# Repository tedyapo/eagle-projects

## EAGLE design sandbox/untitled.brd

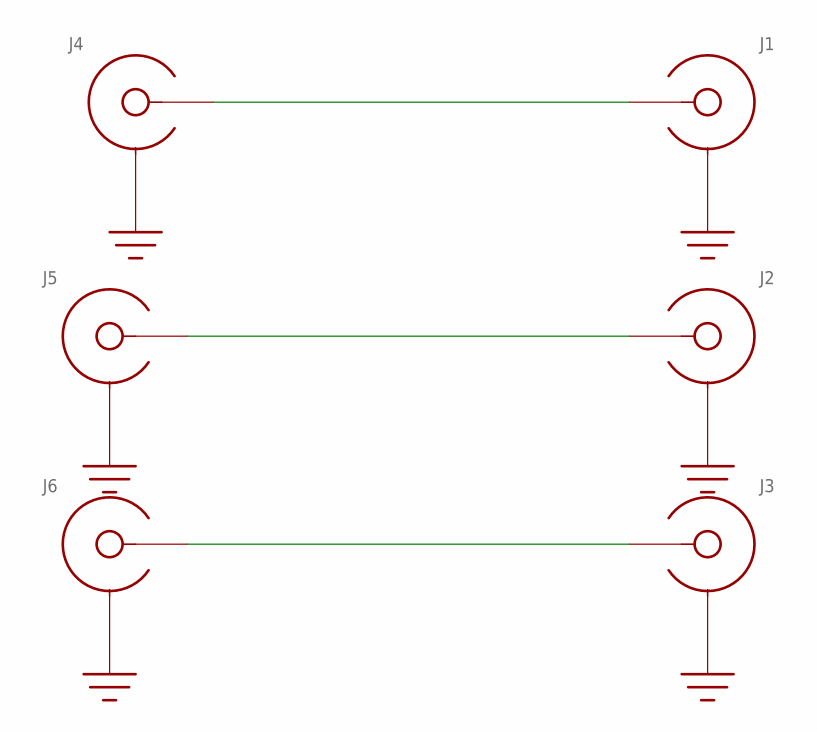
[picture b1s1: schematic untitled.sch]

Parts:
J1, J4: SMA-EDGE-LAUNCH4020_TAPER; SMA_EDGE_LAUNCH_2L_4020_TAPER
J2, J5: SMA-EDGE-LAUNCH4L-4020-TAPER-FIXED; SMA_EDGE_LAUNCH_4L_4020_TAPER_FIXED
J3, J6: SMA-EDGE-LAUNCHCUT-PIN; SMA_EDGE_LAUNCH_2L_4020_CUT_PIN

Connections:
GND: J1.BOTTOM_GND (SHIELD), J1.GND@1 (SHIELD), J1.GND@2 (SHIELD), J1.GND@3 (SHIELD), J1.GND@4 (SHIELD), J1.GND@5 (SHIELD), J1.GND@6 (SHIELD), J1.GND@7 (SHIELD), J1.GND@8 (SHIELD), J1.GND@14 (SHIELD), J1.GND@15 (SHIELD), J1.GND@16 (SHIELD), J1.GND@17 (SHIELD), J1.GND_PAD1 (SHIELD), J1.GND_PAD2 (SHIELD), J1.P$1 (SHIELD), J1.P$2 (SHIELD), J2.BOTTOM_GND (SHIELD), J2.GND@1 (SHIELD), J2.GND@2 (SHIELD), J2.GND@3 (SHIELD), J2.GND@4 (SHIELD), J2.GND@5 (SHIELD), J2.GND@6 (SHIELD), J2.GND@7 (SHIELD), J2.GND@8 (SHIELD), J2.GND@14 (SHIELD), J2.GND@15 (SHIELD), J2.GND@16 (SHIELD), J2.GND@17 (SHIELD), J2.GND_PAD1 (SHIELD), J2.GND_PAD2 (SHIELD), J2.P$1 (SHIELD), J2.P$2 (SHIELD), J3.BOTTOM_GND (SHIELD), J3.GND@1 (SHIELD), J3.GND@2 (SHIELD), J3.GND@3 (SHIELD), J3.GND@4 (SHIELD), J3.GND@5 (SHIELD), J3.GND@6 (SHIELD), J3.GND@7 (SHIELD), J3.GND@8 (SHIELD), J3.GND@14 (SHIELD), J3.GND@15 (SHIELD), J3.GND@16 (SHIELD), J3.GND@17 (SHIELD), J3.GND_PAD1 (SHIELD), J3.GND_PAD2 (SHIELD), J4.BOTTOM_GND (SHIELD), J4.GND@1 (SHIELD), J4.GND@2 (SHIELD), J4.GND@3 (SHIELD), J4.GND@4 (SHIELD), J4.GND@5 (SHIELD), J4.GND@6 (SHIELD), J4.GND@7 (SHIELD), J4.GND@8 (SHIELD), J4.GND@14 (SHIELD), J4.GND@15 (SHIELD), J4.GND@16 (SHIELD), J4.GND@17 (SHIELD), J4.GND_PAD1 (SHIELD), J4.GND_PAD2 (SHIELD), J4.P$1 (SHIELD), J4.P$2 (SHIELD), J5.BOTTOM_GND (SHIELD), J5.GND@1 (SHIELD), J5.GND@2 (SHIELD), J5.GND@3 (SHIELD), J5.GND@4 (SHIELD), J5.GND@5 (SHIELD), J5.GND@6 (SHIELD), J5.GND@7 (SHIELD), J5.GND@8 (SHIELD), J5.GND@14 (SHIELD), J5.GND@15 (SHIELD), J5.GND@16 (SHIELD), J5.GND@17 (SHIELD), J5.GND_PAD1 (SHIELD), J5.GND_PAD2 (SHIELD), J5.P$1 (SHIELD), J5.P$2 (SHIELD), J6.BOTTOM_GND (SHIELD), J6.GND@1 (SHIELD), J6.GND@2 (SHIELD), J6.GND@3 (SHIELD), J6.GND@4 (SHIELD), J6.GND@5 (SHIELD), J6.GND@6 (SHIELD), J6.GND@7 (SHIELD), J6.GND@8 (SHIELD), J6.GND@14 (SHIELD), J6.GND@15 (SHIELD), J6.GND@16 (SHIELD), J6.GND@17 (SHIELD), J6.GND_PAD1 (SHIELD), J6.GND_PAD2 (SHIELD)
unnamed: J1.CENTER@1 (CENTER), J4.CENTER@1 (CENTER)
unnamed: J2.CENTER@1 (CENTER), J2.P$3 (CENTER), J5.CENTER@1 (CENTER), J5.P$3 (CENTER)
unnamed: J3.CENTER@1 (CENTER), J3.CENTER@3 (CENTER), J6.CENTER@1 (CENTER), J6.CENTER@3 (CENTER)

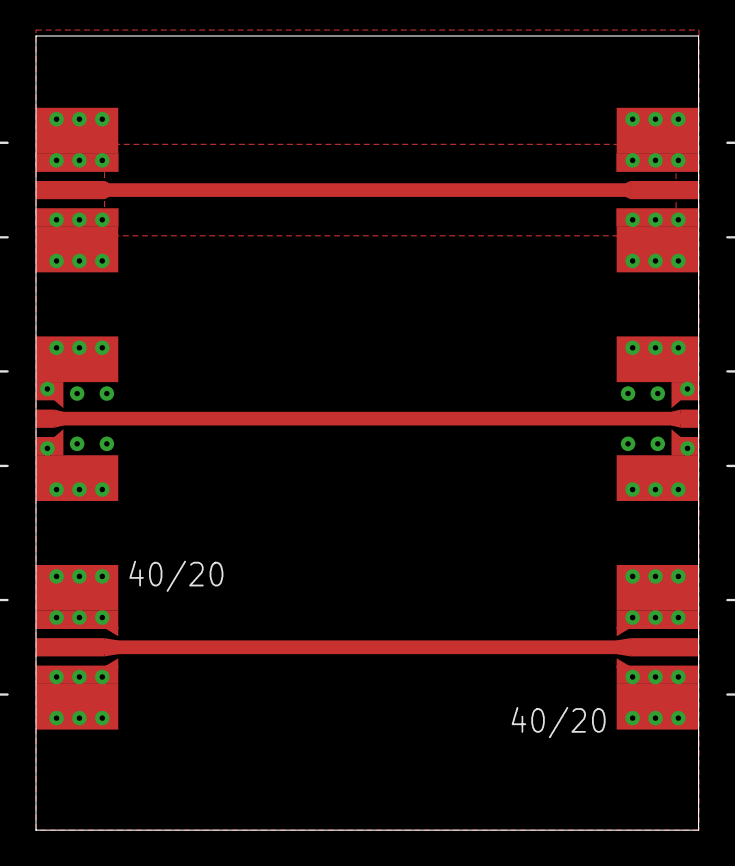
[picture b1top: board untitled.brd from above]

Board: 2 copper layers, 36.8 x 44.1 mm, 6 parts (0 on the bottom side), 4 nets.

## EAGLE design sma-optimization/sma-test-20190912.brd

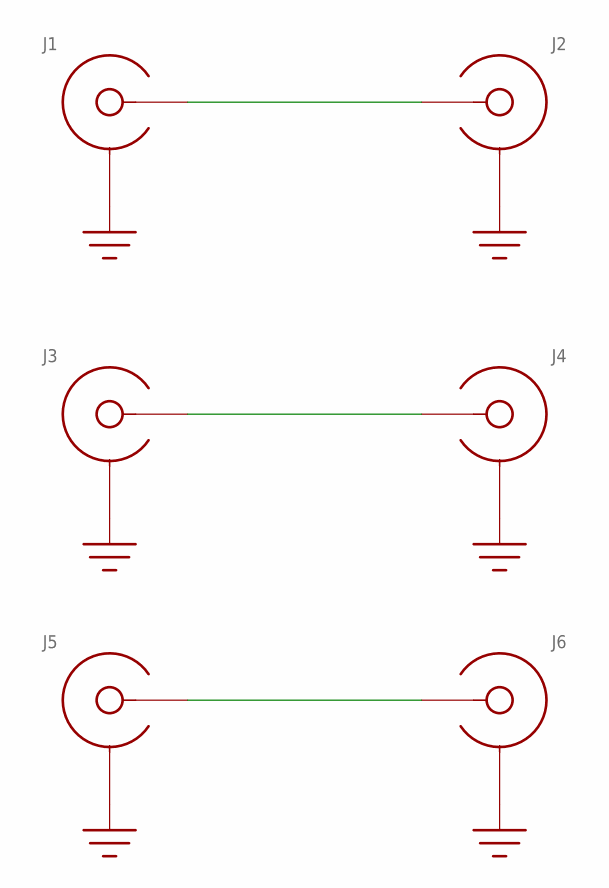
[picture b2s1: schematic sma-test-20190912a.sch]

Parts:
J1: SMA-EDGE-LAUNCH4020N; SMA_EDGE_LAUNCH_4L_4020_N
J2: SMA-EDGE-LAUNCH4020N1; SMA_EDGE_LAUNCH_4L_4020_N1
J3: SMA-EDGE-LAUNCH4020N2; SMA_EDGE_LAUNCH_4L_4020_N2
J4: SMA-EDGE-LAUNCH4020N3; SMA_EDGE_LAUNCH_4L_4020_N3
J5: SMA-EDGE-LAUNCH4020N4; SMA_EDGE_LAUNCH_4L_4020_N4
J6: SMA-EDGE-LAUNCH4L-4020-TAPER-FIXED; SMA_EDGE_LAUNCH_4L_4020_TAPER_FIXED

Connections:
GND: J1.BOTTOM_GND (SHIELD), J1.GND@1 (SHIELD), J1.GND@2 (SHIELD), J1.GND@3 (SHIELD), J1.GND@4 (SHIELD), J1.GND@5 (SHIELD), J1.GND@6 (SHIELD), J1.GND@7 (SHIELD), J1.GND@8 (SHIELD), J1.GND@14 (SHIELD), J1.GND@15 (SHIELD), J1.GND@16 (SHIELD), J1.GND@17 (SHIELD), J1.GND_PAD1 (SHIELD), J1.GND_PAD2 (SHIELD), J1.P$1 (SHIELD), J1.P$2 (SHIELD), J2.BOTTOM_GND (SHIELD), J2.GND@1 (SHIELD), J2.GND@2 (SHIELD), J2.GND@3 (SHIELD), J2.GND@4 (SHIELD), J2.GND@5 (SHIELD), J2.GND@6 (SHIELD), J2.GND@7 (SHIELD), J2.GND@8 (SHIELD), J2.GND@14 (SHIELD), J2.GND@15 (SHIELD), J2.GND@16 (SHIELD), J2.GND@17 (SHIELD), J2.GND_PAD1 (SHIELD), J2.GND_PAD2 (SHIELD), J2.P$1 (SHIELD), J2.P$2 (SHIELD), J3.BOTTOM_GND (SHIELD), J3.GND@1 (SHIELD), J3.GND@2 (SHIELD), J3.GND@3 (SHIELD), J3.GND@4 (SHIELD), J3.GND@5 (SHIELD), J3.GND@6 (SHIELD), J3.GND@7 (SHIELD), J3.GND@8 (SHIELD), J3.GND@14 (SHIELD), J3.GND@15 (SHIELD), J3.GND@16 (SHIELD), J3.GND@17 (SHIELD), J3.GND_PAD1 (SHIELD), J3.GND_PAD2 (SHIELD), J3.P$1 (SHIELD), J3.P$2 (SHIELD), J4.BOTTOM_GND (SHIELD), J4.GND@1 (SHIELD), J4.GND@2 (SHIELD), J4.GND@3 (SHIELD), J4.GND@4 (SHIELD), J4.GND@5 (SHIELD), J4.GND@6 (SHIELD), J4.GND@7 (SHIELD), J4.GND@8 (SHIELD), J4.GND@14 (SHIELD), J4.GND@15 (SHIELD), J4.GND@16 (SHIELD), J4.GND@17 (SHIELD), J4.GND_PAD1 (SHIELD), J4.GND_PAD2 (SHIELD), J4.P$1 (SHIELD), J4.P$2 (SHIELD), J5.BOTTOM_GND (SHIELD), J5.GND@1 (SHIELD), J5.GND@2 (SHIELD), J5.GND@3 (SHIELD), J5.GND@4 (SHIELD), J5.GND@5 (SHIELD), J5.GND@6 (SHIELD), J5.GND@7 (SHIELD), J5.GND@8 (SHIELD), J5.GND@14 (SHIELD), J5.GND@15 (SHIELD), J5.GND@16 (SHIELD), J5.GND@17 (SHIELD), J5.GND_PAD1 (SHIELD), J5.GND_PAD2 (SHIELD), J5.P$1 (SHIELD), J5.P$2 (SHIELD), J6.BOTTOM_GND (SHIELD), J6.GND@1 (SHIELD), J6.GND@2 (SHIELD), J6.GND@3 (SHIELD), J6.GND@4 (SHIELD), J6.GND@5 (SHIELD), J6.GND@6 (SHIELD), J6.GND@7 (SHIELD), J6.GND@8 (SHIELD), J6.GND@14 (SHIELD), J6.GND@15 (SHIELD), J6.GND@16 (SHIELD), J6.GND@17 (SHIELD), J6.GND_PAD1 (SHIELD), J6.GND_PAD2 (SHIELD), J6.P$1 (SHIELD), J6.P$2 (SHIELD)
unnamed: J1.CENTER@1 (CENTER), J1.CENTER@2 (CENTER), J2.CENTER@1 (CENTER), J2.CENTER@2 (CENTER)
unnamed: J3.CENTER@1 (CENTER), J3.CENTER@2 (CENTER), J4.CENTER@1 (CENTER), J4.CENTER@2 (CENTER)
unnamed: J5.CENTER@1 (CENTER), J5.CENTER@2 (CENTER), J6.CENTER@1 (CENTER), J6.CENTER@2

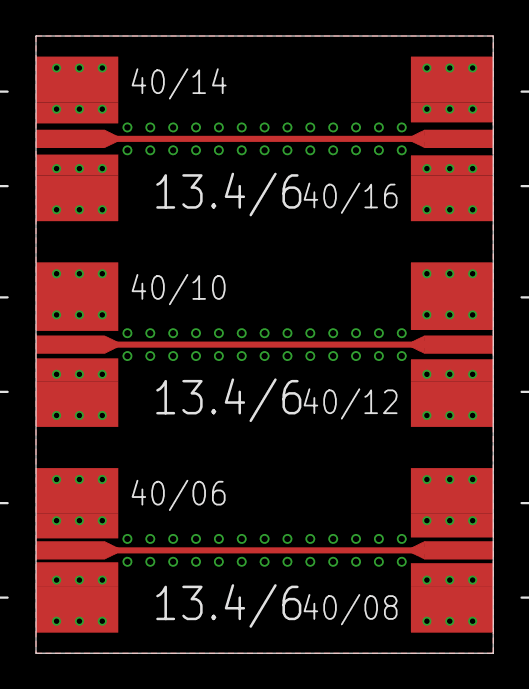
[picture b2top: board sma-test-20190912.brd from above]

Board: 4 copper layers, 25.4 x 34.3 mm, 6 parts (0 on the bottom side), 4 nets.

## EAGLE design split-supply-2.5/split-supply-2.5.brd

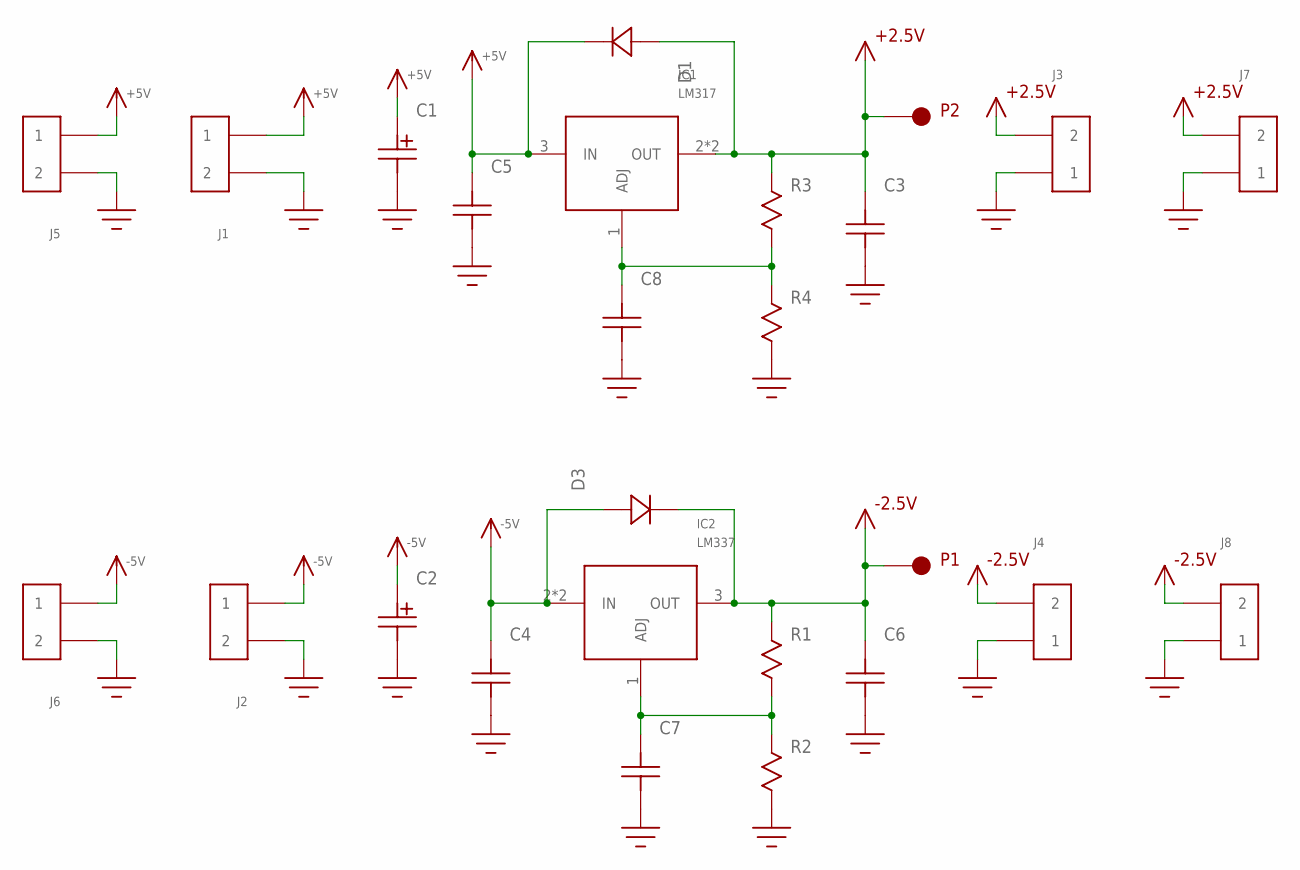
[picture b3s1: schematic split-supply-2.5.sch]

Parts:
C1, C2: C-POLARIZED; CAP-E61
C3, C4, C5, C6: C1206; 1206
C7, C8: C0603
D1, D3: DIODE; DO-214(SMA)
IC1: LM317; SOT-223
IC2: LM337; SOT-223
J1, J2, J3, J4: HEADER_2PIN
J5, J6, J7, J8: HEADER_2PINSCREW-TERM; FCI_20020316_SCREW_TERM_2P
P1, P2: ICSP_PAD
R1, R2, R3, R4: R0603

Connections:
+2.5V: C3.P$2, D1.C (CATHODE), IC1.2 (OUT), IC1.4 (OUT), J3.2, J7.P$2 (2), P2.P$1, R3.P$1
+5V: C1.+, C5.P$2, D1.A (ANODE), IC1.3 (IN), J1.1, J5.P$1 (1)
-2.5V: C6.P$2, D3.A (ANODE), IC2.3 (OUT), J4.2, J8.P$2 (2), P1.P$1, R1.P$1
-5V: C2.+, C4.P$2, D3.C (CATHODE), IC2.2 (IN), IC2.4 (IN), J2.1, J6.P$1 (1)
GND: C1.-, C2.-, C3.P$1, C4.P$1, C5.P$1, C6.P$1, C7.P$1, C8.P$1, J1.2, J2.2, J3.1, J4.1, J5.P$2 (2), J6.P$2 (2), J7.P$1 (1), J8.P$1 (1), R2.P$2, R4.P$2
unnamed: C7.P$2, IC2.1 (ADJ), R1.P$2, R2.P$1
unnamed: C8.P$2, IC1.1 (ADJ), R3.P$2, R4.P$1

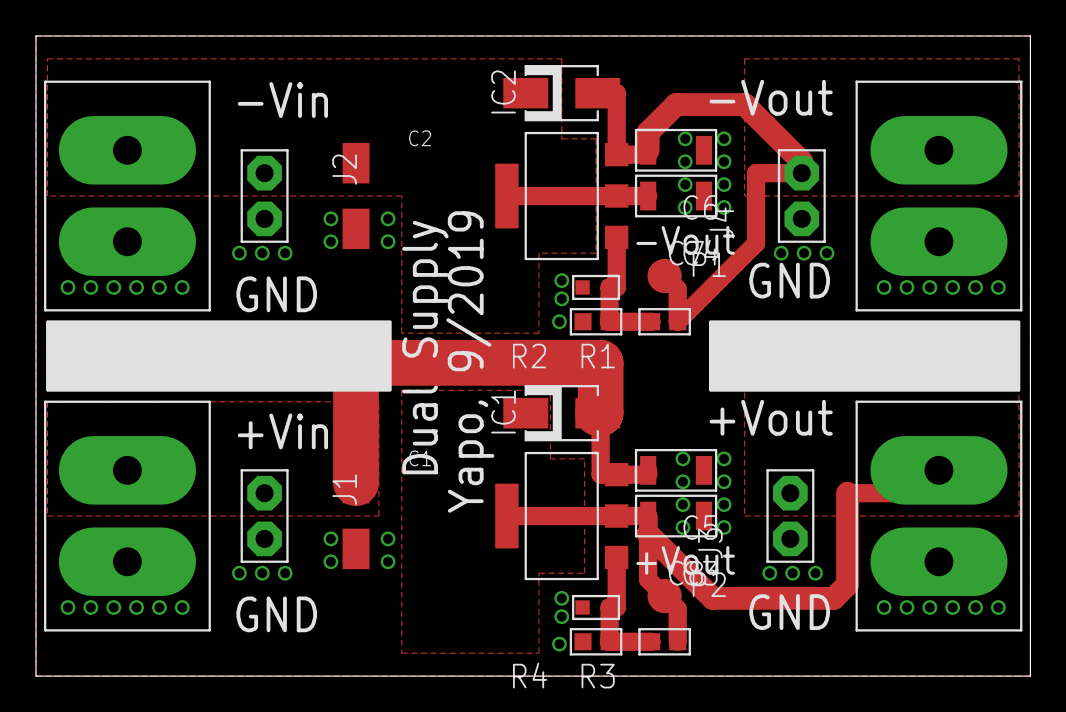
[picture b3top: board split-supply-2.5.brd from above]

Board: 2 copper layers, 55.2 x 35.6 mm, 26 parts (0 on the bottom side), 7 nets.

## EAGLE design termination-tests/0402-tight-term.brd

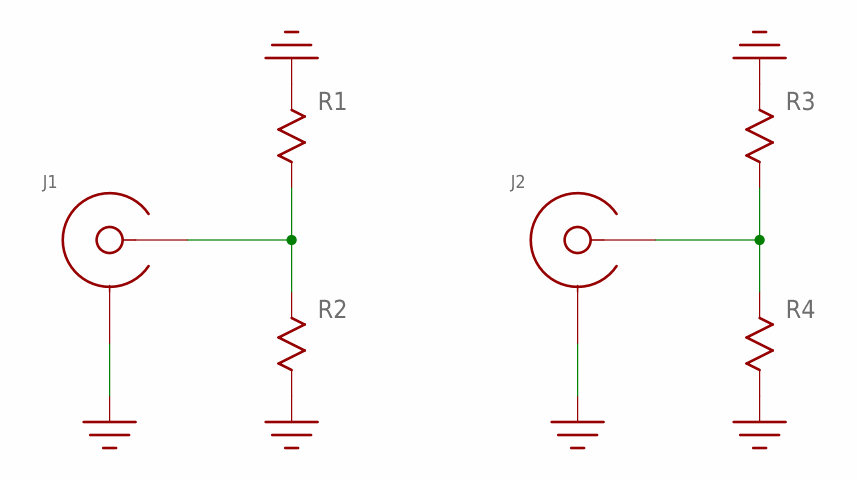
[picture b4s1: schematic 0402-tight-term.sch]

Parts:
J1, J2: SMA-EDGE-LAUNCH4020_TAPER; SMA_EDGE_LAUNCH_2L_4020_TAPER
R1, R2: R0402-TIGHT; 0402-TIGHT
R3, R4: R0402; 0402

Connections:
GND: J1.BOTTOM_GND (SHIELD), J1.GND@1 (SHIELD), J1.GND@2 (SHIELD), J1.GND@3 (SHIELD), J1.GND@4 (SHIELD), J1.GND@5 (SHIELD), J1.GND@6 (SHIELD), J1.GND@7 (SHIELD), J1.GND@8 (SHIELD), J1.GND@14 (SHIELD), J1.GND@15 (SHIELD), J1.GND@16 (SHIELD), J1.GND@17 (SHIELD), J1.GND_PAD1 (SHIELD), J1.GND_PAD2 (SHIELD), J1.P$1 (SHIELD), J1.P$2 (SHIELD), J2.BOTTOM_GND (SHIELD), J2.GND@1 (SHIELD), J2.GND@2 (SHIELD), J2.GND@3 (SHIELD), J2.GND@4 (SHIELD), J2.GND@5 (SHIELD), J2.GND@6 (SHIELD), J2.GND@7 (SHIELD), J2.GND@8 (SHIELD), J2.GND@14 (SHIELD), J2.GND@15 (SHIELD), J2.GND@16 (SHIELD), J2.GND@17 (SHIELD), J2.GND_PAD1 (SHIELD), J2.GND_PAD2 (SHIELD), J2.P$1 (SHIELD), J2.P$2 (SHIELD), R1.P$1, R2.P$2, R3.1, R4.2
unnamed: J1.CENTER@1 (CENTER), R1.P$2, R2.P$1
unnamed: J2.CENTER@1 (CENTER), R3.2, R4.1

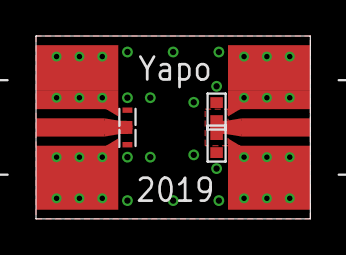
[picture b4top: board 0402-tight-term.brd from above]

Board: 2 copper layers, 15.2 x 10.2 mm, 6 parts (0 on the bottom side), 3 nets.

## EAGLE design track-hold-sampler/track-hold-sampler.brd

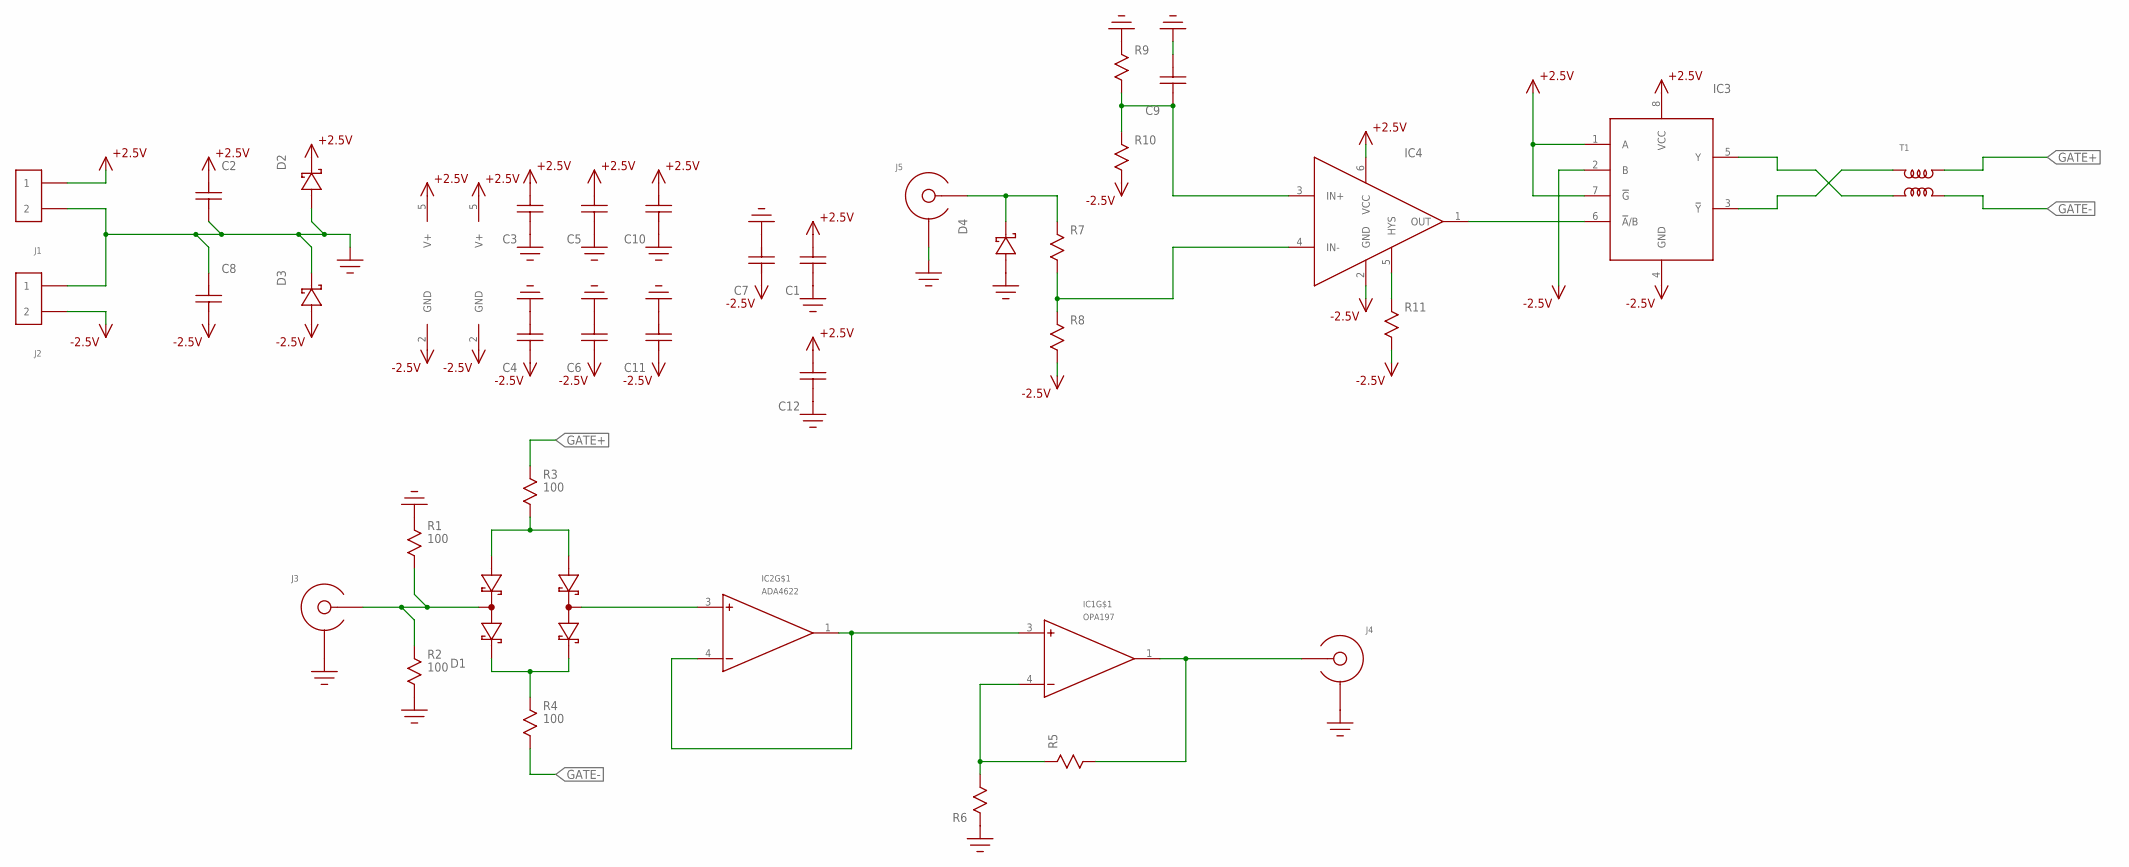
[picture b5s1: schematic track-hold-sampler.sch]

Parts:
C1, C7, C12: C0603
C2, C8: C1206; 1206
C3, C4, C5, C6, C9, C10, C11: C; C0402
D1: SMS3923-081; SC-88
D2, D3, D4: SCHOTTKYSOT-23; SOT-23
IC1: OPA197; TSOT-23
IC2: ADA4622; SOT23-5
IC3: 74LVC2G157; SSOP8
IC4: ADCMP601; SC70-6
J1, J2: HEADER_2PIN
J3, J4, J5: SMA-EDGE-LAUNCH4020N5; SMA_EDGE_LAUNCH_4L_4020_N5
R1, R2, R3, R4: 100; 0402
R5, R6, R7, R8, R9, R10, R11: R0603
T1: MABA007159; MABAES0061

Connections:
+2.5V: C1.P$1, C2.P$2, C3.1, C5.1, C10.1, C12.P$1, D2.3 (CATHODE), IC1.5 (V+), IC2.5 (V+), IC3.1 (A), IC3.7 (!G!), IC3.8 (VCC), IC4.6 (VCC), J1.1
-2.5V: C4.2, C6.2, C7.P$2, C8.P$1, C11.2, D3.1 (ANODE), IC1.2 (GND), IC2.2 (GND), IC3.2 (B), IC3.4 (GND), IC4.2 (GND), J2.2, R8.P$2, R10.P$2, R11.P$2
GATE+: R3.1, T1.1
GATE-: R4.2, T1.3
GND: C1.P$2, C2.P$1, C3.2, C4.1, C5.2, C6.1, C7.P$1, C8.P$2, C9.1, C10.2, C11.1, C12.P$2, D2.1 (ANODE), D3.3 (CATHODE), D4.1 (ANODE), J1.2, J2.1, J3.BOTTOM_GND (SHIELD), J3.GND@1 (SHIELD), J3.GND@2 (SHIELD), J3.GND@3 (SHIELD), J3.GND@4 (SHIELD), J3.GND@5 (SHIELD), J3.GND@6 (SHIELD), J3.GND@7 (SHIELD), J3.GND@8 (SHIELD), J3.GND@9 (SHIELD), J3.GND@10 (SHIELD), J3.GND@14 (SHIELD), J3.GND@15 (SHIELD), J3.GND@16 (SHIELD), J3.GND@17 (SHIELD), J3.GND_PAD1 (SHIELD), J3.GND_PAD2 (SHIELD), J3.P$1 (SHIELD), J3.P$2 (SHIELD), J3.P$3 (SHIELD), J3.P$4 (SHIELD), J3.P$5 (SHIELD), J4.BOTTOM_GND (SHIELD), J4.GND@1 (SHIELD), J4.GND@2 (SHIELD), J4.GND@3 (SHIELD), J4.GND@4 (SHIELD), J4.GND@5 (SHIELD), J4.GND@6 (SHIELD), J4.GND@7 (SHIELD), J4.GND@8 (SHIELD), J4.GND@9 (SHIELD), J4.GND@10 (SHIELD), J4.GND@14 (SHIELD), J4.GND@15 (SHIELD), J4.GND@16 (SHIELD), J4.GND@17 (SHIELD), J4.GND_PAD1 (SHIELD), J4.GND_PAD2 (SHIELD), J4.P$1 (SHIELD), J4.P$2 (SHIELD), J4.P$3 (SHIELD), J4.P$4 (SHIELD), J4.P$5 (SHIELD), J5.BOTTOM_GND (SHIELD), J5.GND@1 (SHIELD), J5.GND@2 (SHIELD), J5.GND@3 (SHIELD), J5.GND@4 (SHIELD), J5.GND@5 (SHIELD), J5.GND@6 (SHIELD), J5.GND@7 (SHIELD), J5.GND@8 (SHIELD), J5.GND@9 (SHIELD), J5.GND@10 (SHIELD), J5.GND@14 (SHIELD), J5.GND@15 (SHIELD), J5.GND@16 (SHIELD), J5.GND@17 (SHIELD), J5.GND_PAD1 (SHIELD), J5.GND_PAD2 (SHIELD), J5.P$1 (SHIELD), J5.P$2 (SHIELD), J5.P$3 (SHIELD), J5.P$4 (SHIELD), J5.P$5 (SHIELD), R1.1, R2.2, R6.P$1, R9.P$1
unnamed: D1.2 (COMMON0), J3.CENTER@1 (CENTER), J3.CENTER@2 (CENTER), R1.2, R2.1
unnamed: D1.1 (ANODE0), D1.6 (ANODE1), R3.2
unnamed: IC1.3 (+), IC2.1 (OUT), IC2.4 (-)
unnamed: IC1.4 (-), R5.P$1, R6.P$2
unnamed: IC1.1 (OUT), J4.CENTER@1 (CENTER), J4.CENTER@2 (CENTER), R5.P$2
unnamed: D1.5 (COMMON1), IC2.3 (+)
unnamed: D1.3 (CATHODE0), D1.4 (CATHODE1), R4.1
unnamed: IC3.6 (!A!/B), IC4.1 (OUT)
unnamed: D4.3 (CATHODE), J5.CENTER@1 (CENTER), J5.CENTER@2 (CENTER), R7.P$1
unnamed: IC4.4 (IN-), R7.P$2, R8.P$1
unnamed: IC4.5 (HYS), R11.P$1
unnamed: C9.2, IC4.3 (IN+), R9.P$2, R10.P$1
unnamed: IC3.5 (Y), T1.4
unnamed: IC3.3 (!Y!), T1.5

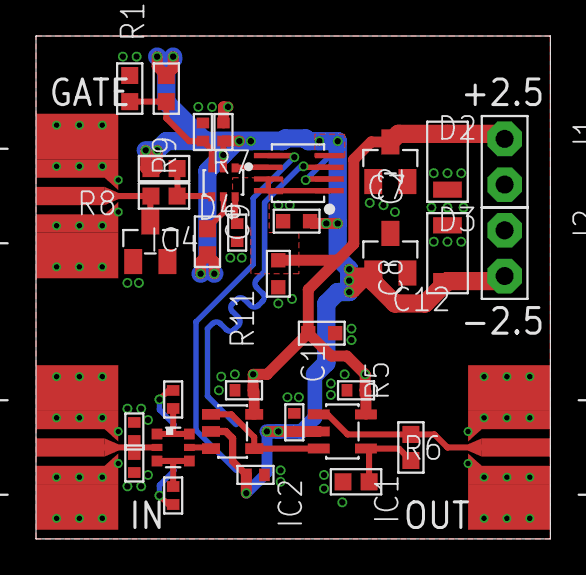
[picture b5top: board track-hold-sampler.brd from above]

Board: 4 copper layers, 28.6 x 27.9 mm, 37 parts (1 on the bottom side), 19 nets.

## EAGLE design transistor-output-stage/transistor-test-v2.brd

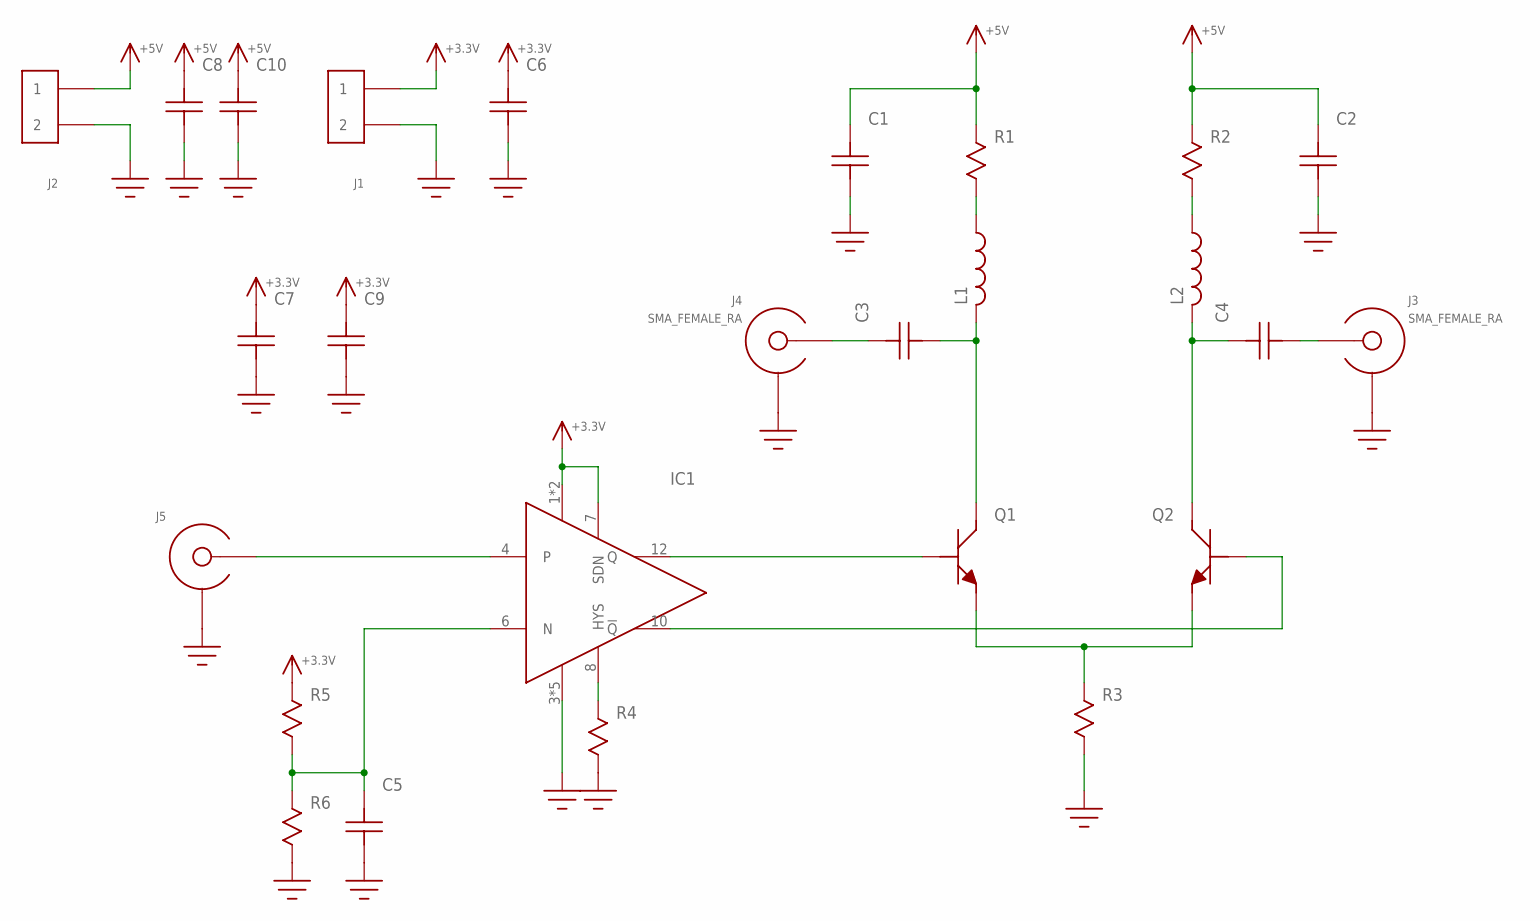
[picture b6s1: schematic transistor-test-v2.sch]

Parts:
C1, C2, C3, C4, C5, C7, C9: C0603
C6, C8, C10: C1206; 1206
IC1: ADCMP607; QFN12-3X3
J1, J2: HEADER_2PIN
J3, J4: SMA_FEMALE_RA; SMA_RA_PCB
J5: SMA_END_LAUNCH2L; SMA_EDGE_LAUNCH_2L
L1, L2: INDUCTOR; R0603
Q1, Q2: MCH4020; SOT343
R1, R2, R3, R4, R5, R6: R0603

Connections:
+3.3V: C6.P$2, C7.P$2, C9.P$2, IC1.1 (VCC), IC1.2 (VCC), IC1.7 (SDN), J1.1, R5.P$1
+5V: C1.P$2, C2.P$2, C8.P$2, C10.P$2, J2.1, R1.P$1, R2.P$1
GND: C1.P$1, C2.P$1, C5.P$1, C6.P$1, C7.P$1, C8.P$1, C9.P$1, C10.P$1, IC1.3 (VEE), IC1.5 (VEE), IC1.9 (VEE), IC1.11 (VEE), IC1.EP (VEE), J1.2, J2.2, J3.SHIELD@1 (SHIELD), J3.SHIELD@2 (SHIELD), J3.SHIELD@3 (SHIELD), J3.SHIELD@4 (SHIELD), J4.SHIELD@1 (SHIELD), J4.SHIELD@2 (SHIELD), J4.SHIELD@3 (SHIELD), J4.SHIELD@4 (SHIELD), J5.BOTTOM_GND (SHIELD), J5.GND@1 (SHIELD), J5.GND@2 (SHIELD), J5.GND@3 (SHIELD), J5.GND@4 (SHIELD), J5.GND@5 (SHIELD), J5.GND@6 (SHIELD), J5.GND@7 (SHIELD), J5.GND@8 (SHIELD), J5.GND@11 (SHIELD), J5.GND@12 (SHIELD), J5.GND@14 (SHIELD), J5.GND@15 (SHIELD), J5.GND@16 (SHIELD), J5.GND@17 (SHIELD), J5.GND_PAD1 (SHIELD), J5.GND_PAD2 (SHIELD), R3.P$2, R4.P$2, R6.P$2
unnamed: C3.P$1, L1.P$2 (2), Q1.1 (C)
unnamed: C4.P$2, L2.P$2 (2), Q2.1 (C)
unnamed: Q1.2 (E), Q1.4 (E), Q2.2 (E), Q2.4 (E), R3.P$1
unnamed: IC1.12 (Q), Q1.3 (B)
unnamed: IC1.10 (!Q!), Q2.3 (B)
unnamed: C3.P$2, J4.CENTER
unnamed: C4.P$1, J3.CENTER
unnamed: C5.P$2, IC1.6 (N), R5.P$2, R6.P$1
unnamed: IC1.8 (HYS), R4.P$1
unnamed: IC1.4, J5.CENTER@1 (CENTER)
unnamed: L1.P$1 (1), R1.P$2
unnamed: L2.P$1 (1), R2.P$2

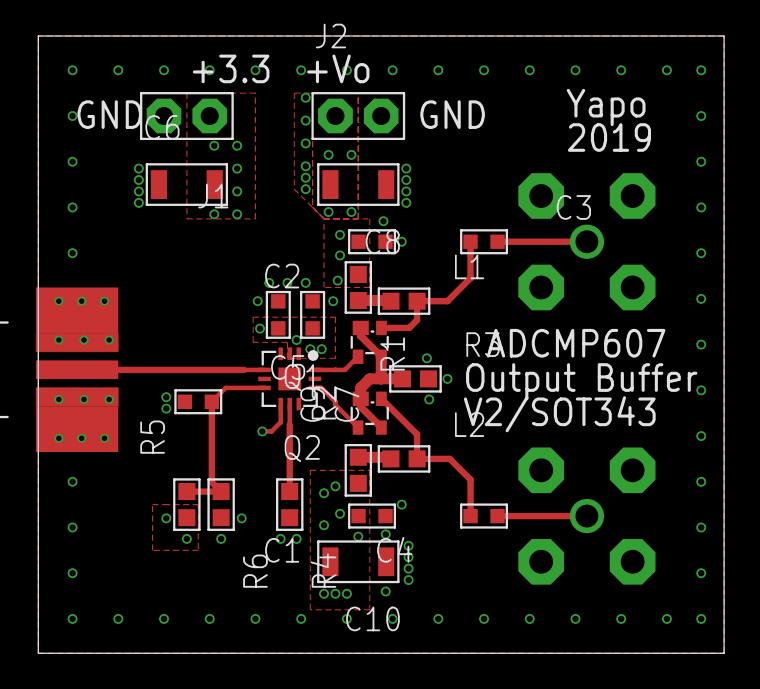
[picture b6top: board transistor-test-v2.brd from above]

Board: 4 copper layers, 38.1 x 34.3 mm, 26 parts (0 on the bottom side), 15 nets.
